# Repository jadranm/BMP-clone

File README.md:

# BMP-clone
black magic probe clone v1.0

PCB je gotov 
checkiraj [prezentaciju](prezentacija.pdf)
 za više informacija

    TVZ diplomski elektrotehnika / Elektrotehničke tehnologije
    [ET] 2023/2024 2. semestar

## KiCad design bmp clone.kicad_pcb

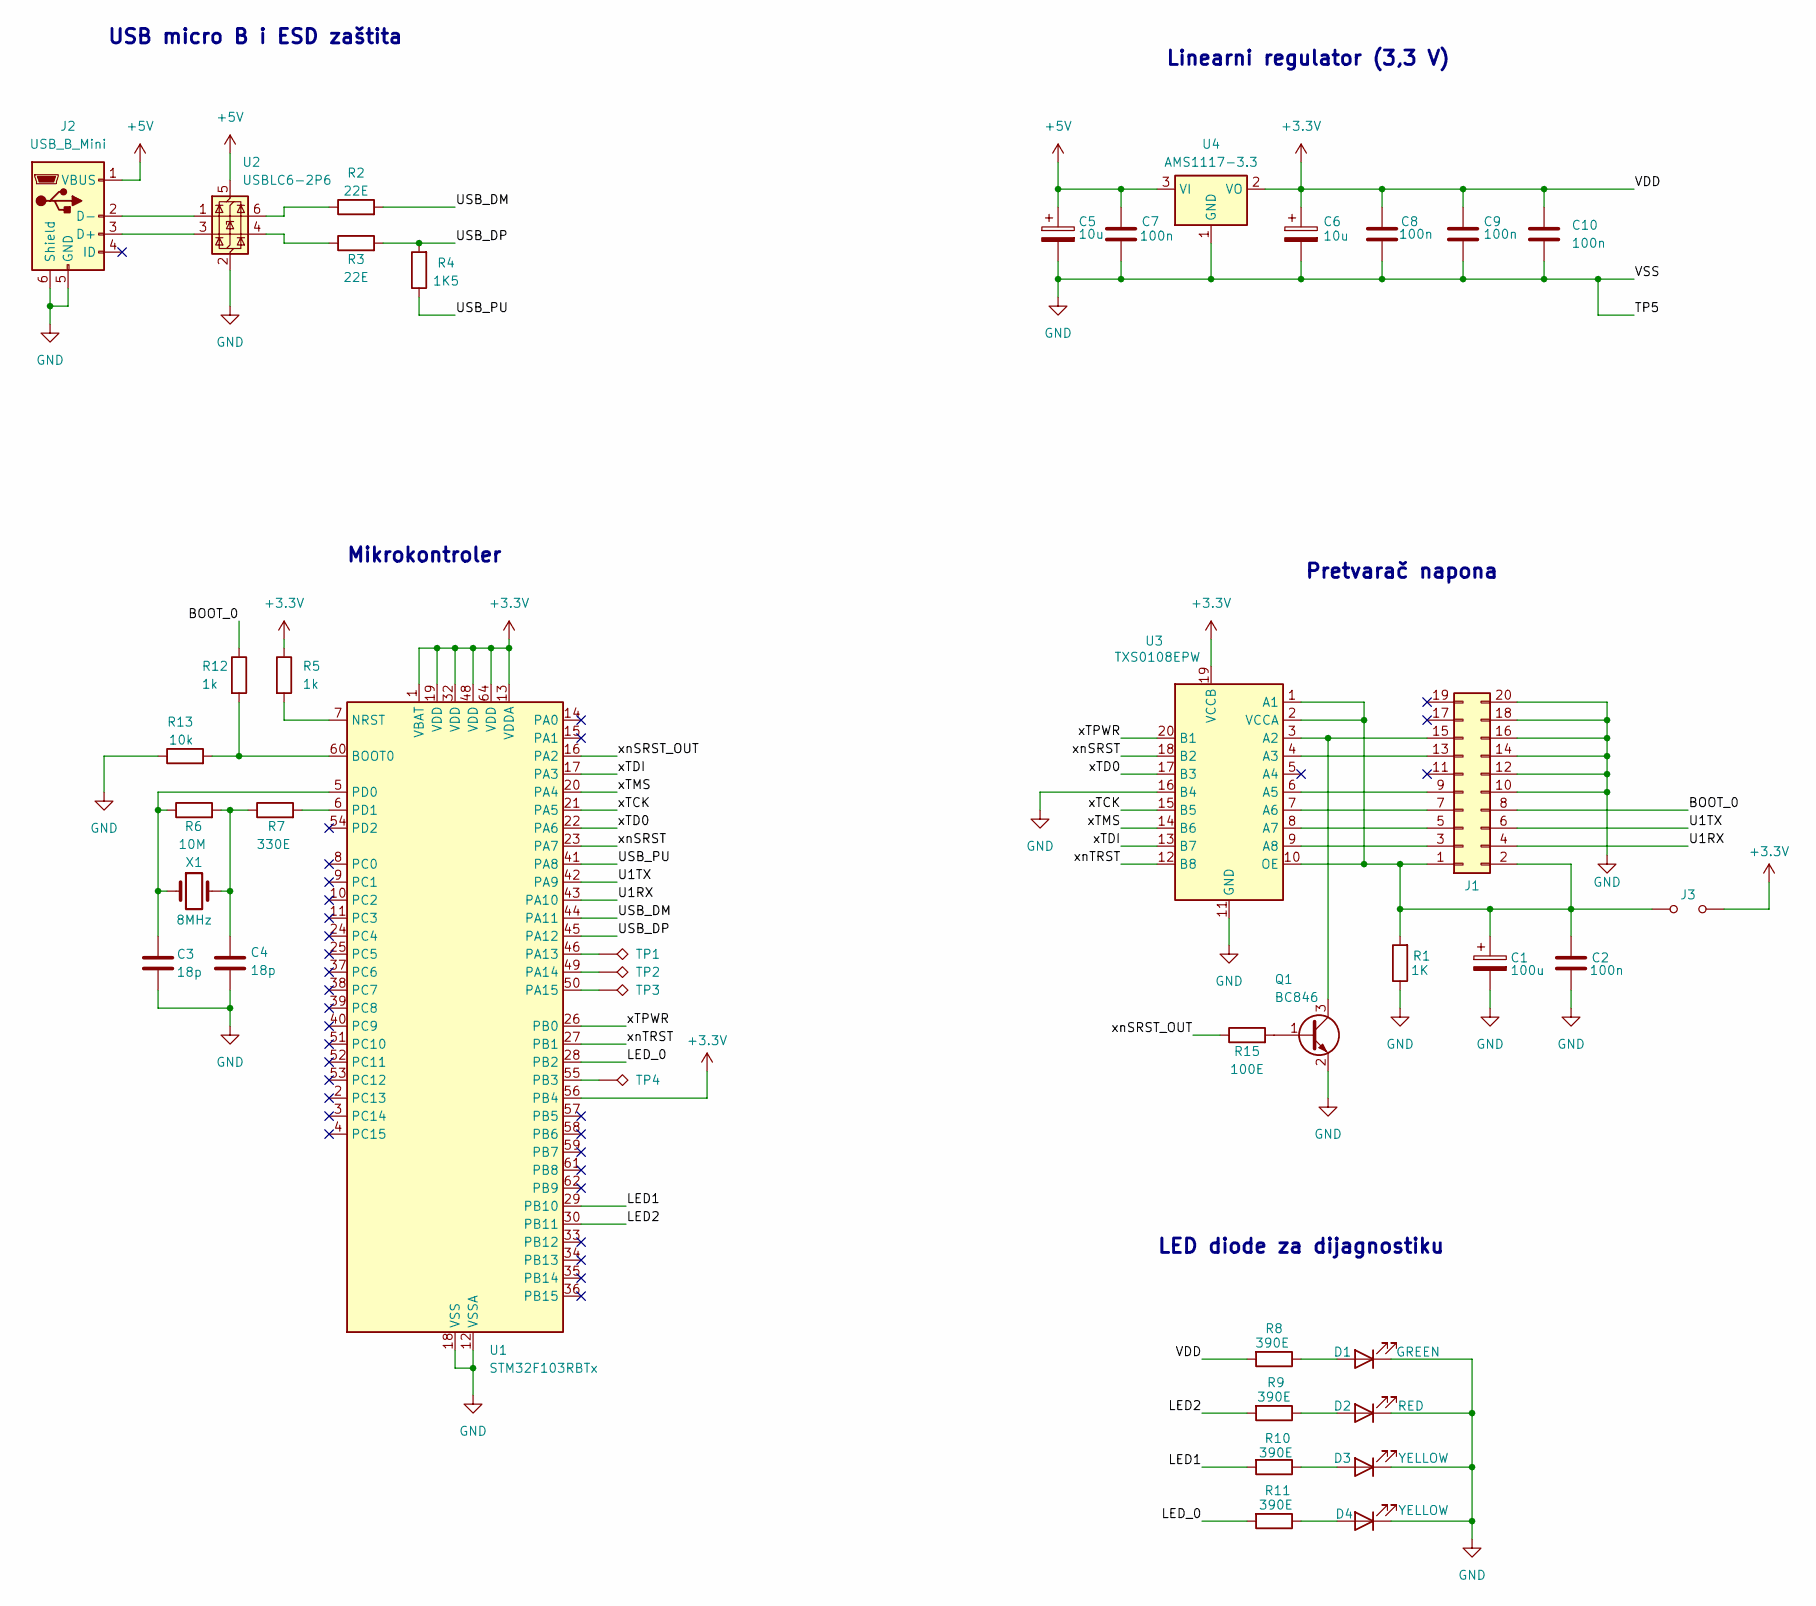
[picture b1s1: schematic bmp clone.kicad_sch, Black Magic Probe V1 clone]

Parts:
C1: 100u; C_0805_2012Metric
C2, C7, C8, C9, C10: 100n; C_0805_2012Metric
C3, C4: 18p; C_0805_2012Metric
C5, C6: 10u; C_0805_2012Metric
D1: GREEN; LED_1206_3216Metric
D2: RED; LED_1206_3216Metric
D3, D4: YELLOW; LED_1206_3216Metric
J1: Conn_02x10_Odd_Even; IDC-Header_2x08_P2.54mm_Vertical
J2: USB_B_Mini; USB_Mini-B_Lumberg_2486_01_Horizontal
J3: Jumper_2_Open; PinHeader_1x02_P1.00mm_Vertical
Q1: BC846; SOT-23
R1: 1K; R_0805_2012Metric
R2, R3: 22E; R_0805_2012Metric
R4: 1K5; R_0805_2012Metric
R5, R12: 1k; R_0805_2012Metric
R6: 10M; R_0805_2012Metric
R7: 330E; R_0805_2012Metric
R8, R9, R10, R11: 390E; R_0805_2012Metric
R13: 10k; R_0805_2012Metric
R15: 100E; R_0805_2012Metric
TP1, TP2, TP3, TP4: TestPoint_Alt; TestPoint_Pad_D1.0mm
U1: STM32F103RBTx; LQFP-64_10x10mm_P0.5mm
U2: USBLC6-2P6; SOT-666
U3: TXS0108EPW; TSSOP-20_4.4x6.5mm_P0.65mm
U4: AMS1117-3.3; SOT-223
X1: 8MHz; Crystal_SMD_3225-4Pin_3.2x2.5mm

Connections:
+3.3V: C6.1, C8.1, C9.1, C10.1, J3.2 (B), R5.1, R8.2, U1.1 (VBAT), U1.13 (VDDA), U1.19 (VDD), U1.32 (VDD), U1.48 (VDD), U1.56 (PB4), U1.64 (VDD), U3.19 (VCCB), U4.2 (VO)
+5V: C5.1, C7.1, J2.1 (VBUS), U2.5 (VBUS), U4.3 (VI)
/BOOT_0: J1.8, R12.1
/LED1: R10.2, U1.29 (PB10)
/LED2: R9.2, U1.30 (PB11)
/LED_0: R11.2, U1.28 (PB2)
/U1RX: J1.4, U1.43 (PA10)
/U1TX: J1.6, U1.42 (PA9)
/USB_DM: R2.2, U1.44 (PA11)
/USB_DP: R3.2, R4.2, U1.45 (PA12)
/USB_PU: R4.1, U1.41 (PA8)
/xTCK: U1.21 (PA5), U3.15 (B5)
/xTD0: U1.22 (PA6), U3.17 (B3)
/xTDI: U1.17 (PA3), U3.13 (B7)
/xTMS: U1.20 (PA4), U3.14 (B6)
/xTPWR: U1.26 (PB0), U3.20 (B1)
/xnSRST: U1.23 (PA7), U3.18 (B2)
/xnSRST_OUT: R15.1, U1.16 (PA2)
/xnTRST: U1.27 (PB1), U3.12 (B8)
GND: C1.2, C2.2, C3.2, C4.2, C5.2, C6.2, C7.2, C8.2, C9.2, C10.2, D1.1 (K), D2.1 (K), D3.1 (K), D4.1 (K), J1.10, J1.12, J1.14, J1.16, J1.18, J1.20, J2.5 (GND), J2.6 (Shield), Q1.2 (E), R1.1, R13.1, U1.12 (VSSA), U1.18 (VSS), U1.31 (VSS), U1.47 (VSS), U1.63 (VSS), U2.2 (GND), U3.11 (GND), U3.16 (B4), U4.1 (GND); also elsewhere on the board
unnamed: C4.1, R6.2, R7.1, X1.2
unnamed 21: D1.2 (A), R8.1; also elsewhere on the board
unnamed: D2.2 (A), R9.1
unnamed: D3.2 (A), R10.1
unnamed: D4.2 (A), R11.1
unnamed: C1.1, C2.1, J1.1, J1.2, J3.1 (A), R1.2, U3.1 (A1), U3.2 (VCCA), U3.10 (OE)
unnamed: J1.3, U3.9 (A8)
unnamed: J1.5, U3.8 (A7)
unnamed: J1.7, U3.7 (A6)
unnamed: J1.9, U3.6 (A5)
unnamed: J1.13, U3.4 (A3)
unnamed: J1.15, Q1.3 (C), U3.3 (A2)
unnamed: J2.3 (D+), U2.3 (I/O2)
unnamed: J2.2 (D-), U2.1 (I/O1)
unnamed: Q1.1 (B), R15.2
unnamed: R2.1, U2.6 (I/O1)
unnamed: R3.1, U2.4 (I/O2)
unnamed: R12.2, R13.2, U1.60 (BOOT0)
unnamed: R5.2, U1.7 (NRST)
unnamed: TP1.1, U1.46 (PA13)
unnamed: TP2.1, U1.49 (PA14)
unnamed: TP3.1, U1.50 (PA15)
unnamed: TP4.1, U1.55 (PB3)
unnamed: C3.1, R6.1, U1.5 (PD0), X1.1
unnamed: R7.2, U1.6 (PD1)

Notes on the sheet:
Mikrokontroler
Linearni regulator (3,3 V)
USB micro B i ESD zaštita
Pretvarač napona
LED diode za dijagnostiku

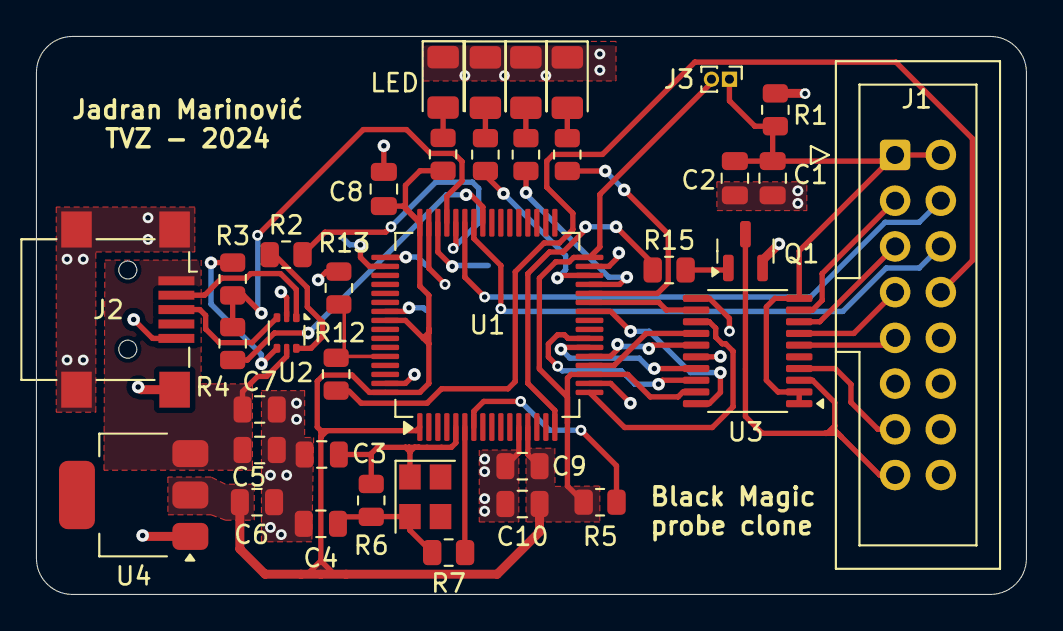
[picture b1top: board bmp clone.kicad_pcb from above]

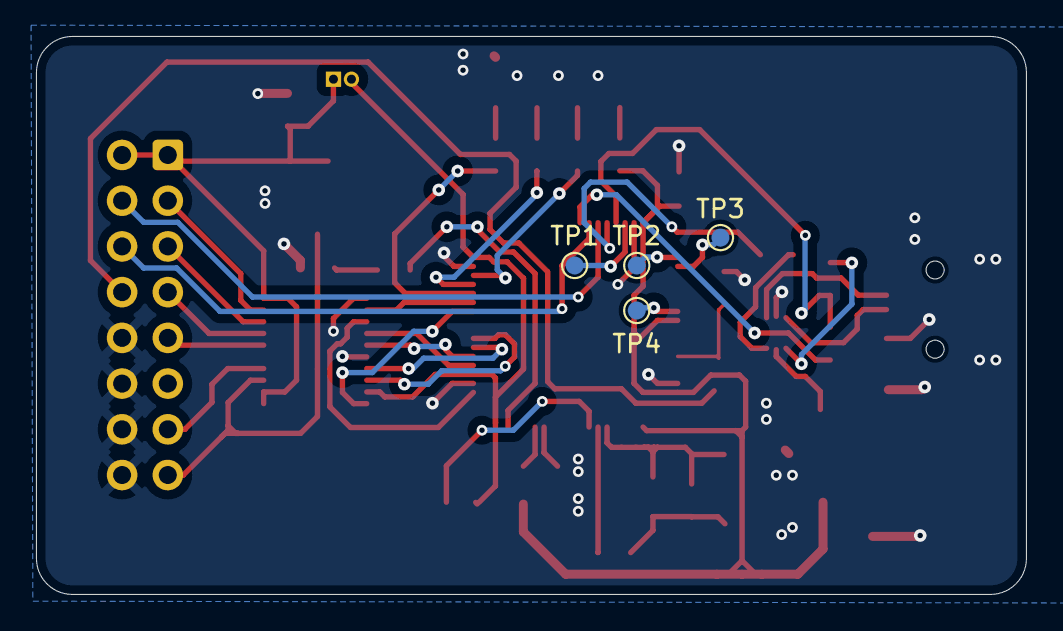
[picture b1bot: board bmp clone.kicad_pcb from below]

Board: 2 copper layers, 55.0 x 31.0 mm, 41 parts (4 on the bottom side), 45 nets.

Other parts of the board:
LED: GREEN; LED_1206_3216Metric

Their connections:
GND: LED.1 (K); also elsewhere on the board
unnamed 21: LED.2 (A); also elsewhere on the board

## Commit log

2024-05-23 elektricna shema
2024-05-23 Update README.md
    readme update
2024-06-04 dodan gitignore
2024-06-27 dodani su gerberi i preza
2024-06-29 manje dorade
